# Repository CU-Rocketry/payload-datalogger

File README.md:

# payload-datalogger

Wirelessly configurable thermocouple data logging PCB implementing four MCP96RL00T on-board thermocouple to I2C converter ICs, an ESP32-C3 MCU, and flash storage.

## Screenshots

## BOM

See [this spreadsheet].(https://docs.google.com/spreadsheets/d/12Mr7GmqM8tnob1ocJkmMWgOL1p1aouqN9iYZXRkocOg/edit?usp=sharing)

**BOM cost:** $65 (on DigiKey, for two boards with attrition)
Does not include cables.

Additionally, batteries should be purchased elsewhere such as the suggested Amazon links to remain economical.

## Firmware

Firmware source code is located in the `src/payload-datalogger` directory.
Source code, for ease of modification by all team members, relies on the Arduino hardware abstraction layer (HAL).
The PlatformIO IDE and toolchain is required to build and debug the firmware, meaning that the minimum prerequisites for payload datalogger firmware development are:
- [Visual Studio Code](https://code.visualstudio.com/download)
- [PlatformIO IDE extension](https://marketplace.visualstudio.com/items?itemName=platformio.platformio-ide)

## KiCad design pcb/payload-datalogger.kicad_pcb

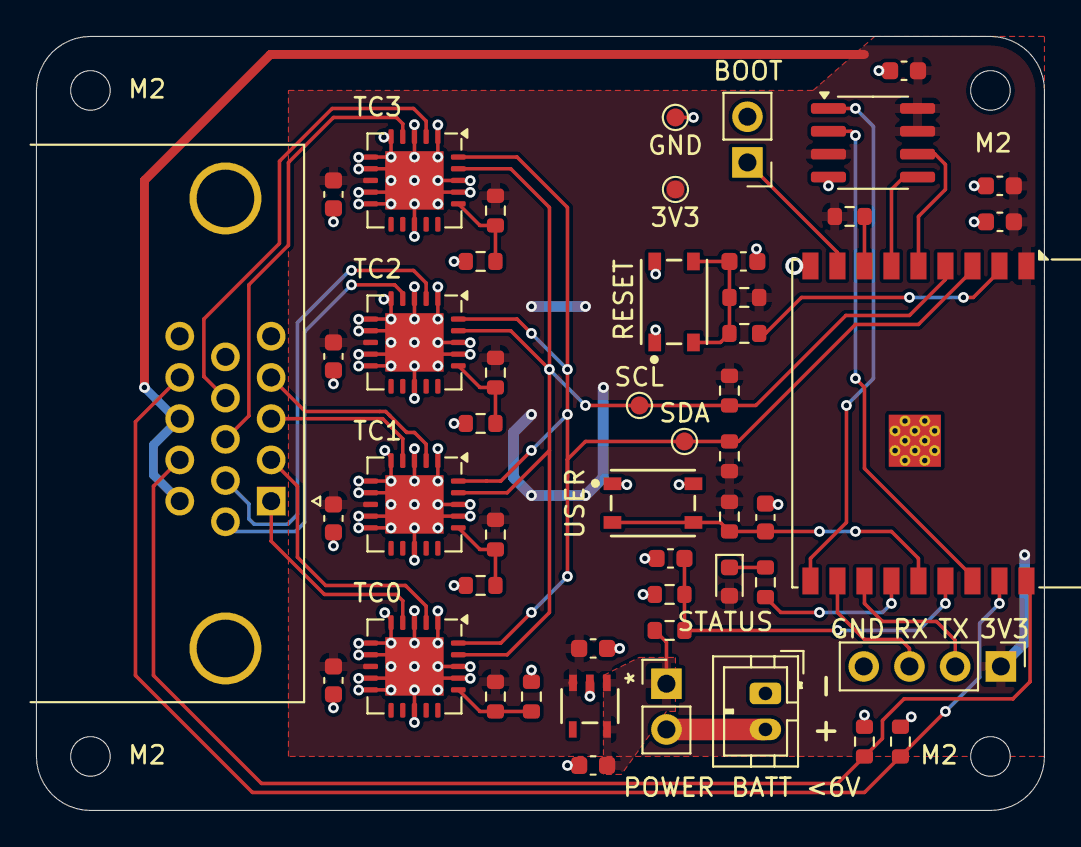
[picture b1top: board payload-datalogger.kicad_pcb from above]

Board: 2 copper layers, 56.0 x 43.0 mm, 50 parts (0 on the bottom side), 34 nets.

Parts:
BT1: 3.7V; JST_PH_B2B-PH-K_1x02_P2.00mm_Vertical
C1, C9, C12, C14: 100n; C_0603_1608Metric
C2, C3, C4, C5, C6, C7, C8: 1u; C_0603_1608Metric
C13: 10u; C_0603_1608Metric
D2: B1911USD; LED_0603_1608Metric
J1: 2.54mm 01x02 header; PinHeader_1x02_P2.54mm_Vertical
J2: DE15 Socket; DSUB-15-HD_Socket_Horizontal_P2.29x2.54mm_EdgePinOffset8.35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
J3: Conn_01x04_Pin; PinHeader_1x04_P2.54mm_Vertical
J4: Conn_01x02_Pin; PinHeader_1x02_P2.54mm_Vertical
R1, R2: 4.7k; R_0603_1608Metric
R3, R4, R7, R9, R11, R13, R14, R15, R16, R18, R19: 10k; R_0603_1608Metric
R5: DNP; R_0603_1608Metric
R6: 0; R_0603_1608Metric
R8: 2.2k; R_0603_1608Metric
R10: 4.3k; R_0603_1608Metric
R12: 7.5k; R_0603_1608Metric
R20: 270; R_0603_1608Metric
SW2, SW3: PTS815; SW_Push_PTS815_SJM_250_SMTR_LFS
TP1: 3V3; TestPoint_Pad_D1.0mm
TP2: GND; TestPoint_Pad_D1.0mm
TP3: I2C_SCL; TestPoint_Pad_D1.0mm
TP4: I2C_SDA; TestPoint_Pad_D1.0mm
U2: BU33SD5; SSOP5_ROM
U3: W25X40CLSN; SOIC-8_3.9x4.9mm_P1.27mm
U4, U5, U6, U7: MCP96RL00T-E_MX; TQFN-20-1EP_5x5mm_P0.65mm_EP3.25x3.25mm
U8: ESP32-C3-WROOM-02

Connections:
+3V3: C3.1, C4.1, C5.1, C6.1, C7.1, C8.1, C13.1, C14.1, D2.2 (A), J2.11, J2.13, J3.1, R1.1, R2.1, R5.2, R7.2, R9.2, R11.2, R15.1, R16.2, R19.1, TP1.1, U2.3 (VOUT), U3.3 (~WP), U3.7 (~HOLD), U3.8 (VCC), U4.8 (VDD), U5.8 (VDD), U6.8 (VDD), U7.8 (VDD), U8.1 (3V3)
+BATT: C2.1, J1.1, R3.1, U2.1 (VIN), U2.5 (STDBY)
/BATT_MEAS: C1.1, R3.2, R4.1, U8.15 (IO3)
/BOOT: J4.1, U8.8 (IO9)
/EN: R18.2, U8.2 (EN)
/FLASH_CLK: U3.6 (CLK), U8.5 (IO6)
/FLASH_CS: U3.1 (~CS), U8.10 (IO10)
/FLASH_DI: U3.5 (DI/IO_{0}), U8.6 (IO7)
/FLASH_DO: U3.2 (DO/IO_{1}), U8.16 (IO2)
/I2C_SCL: R1.2, TP3.1, U4.19 (SCL), U5.19 (SCL), U6.19 (SCL), U7.19 (SCL), U8.4 (IO5)
/I2C_SDA: R2.2, TP4.1, U4.20 (SDA), U5.20 (SDA), U6.20 (SDA), U7.20 (SDA), U8.3 (IO4)
/NTC0-: J2.12, R13.1, U8.18 (IO0)
/NTC1-: J2.14, R14.1, U8.17 (IO1)
/RXD: J3.3, U8.11 (IO20/RXD)
/TC0+: J2.2, U4.2 (VIN+)
/TC0-: J2.1, U4.4 (VIN-)
/TC1+: J2.4, U5.2 (VIN+)
/TC1-: J2.3, U5.4 (VIN-)
/TC2+: J2.7, U6.2 (VIN+)
/TC2-: J2.6, U6.4 (VIN-)
/TC3+: J2.9, U7.2 (VIN+)
/TC3-: J2.8, U7.4 (VIN-)
/TXD: J3.2, U8.12 (IO21/TXD)
/Thermocouple0/I2C_ADDR: R5.1, R6.2, U4.16 (ADDR)
/Thermocouple1/I2C_ADDR: R7.1, R8.2, U5.16 (ADDR)
/Thermocouple2/I2C_ADDR: R9.1, R10.2, U6.16 (ADDR)
/Thermocouple3/I2C_ADDR: R11.1, R12.2, U7.16 (ADDR)
/USER_BTN: C9.1, R15.2, SW2.2, U8.14 (IO19)
/USER_LED: R20.2, U8.13 (IO18)
GND: BT1.1 (+), C1.2, C2.2, C3.2, C4.2, C5.2, C6.2, C7.2, C8.2, C9.2, C12.2, C13.2, C14.2, J2.0, J3.4, J4.2, R4.2, R6.1, R8.1, R10.1, R12.1, R13.2, R14.2, SW2.1, SW3.1, TP2.1, U2.2 (GND), U3.4 (GND), U4.1 (GND), U4.3 (GND), U4.5 (GND), U4.6 (GND), U4.7 (GND), U4.9 (GND), U4.10 (GND), U4.13 (GND), U4.17 (GND), U4.18 (GND), U4.21 (EP), U5.1 (GND), U5.3 (GND), U5.5 (GND), U5.6 (GND), U5.7 (GND), U5.9 (GND), U5.10 (GND), U5.13 (GND), U5.17 (GND), U5.18 (GND), U5.21 (EP), U6.1 (GND), U6.3 (GND), U6.5 (GND), U6.6 (GND), U6.7 (GND), U6.9 (GND), U6.10 (GND), U6.13 (GND), U6.17 (GND), U6.18 (GND), U6.21 (EP), U7.1 (GND), U7.3 (GND), U7.5 (GND), U7.6 (GND), U7.7 (GND), U7.9 (GND), U7.10 (GND), U7.13 (GND), U7.17 (GND), U7.18 (GND), U7.21 (EP), U8.9 (GND), U8.19 (GND)
unnamed: BT1.2 (-), J1.2
unnamed: C12.1, R16.1, R18.1, SW3.2
unnamed: D2.1 (K), R20.1
unnamed: R19.2, U8.7 (IO8)

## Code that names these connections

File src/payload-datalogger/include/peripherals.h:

#ifndef PERIPHERALS_H
#define PERIPHERALS_H

// ADC
#define NTC_0_PIN 0
#define NTC_1_PIN 1
#define BATT_MEAS_PIN 3

// SPI
#define FLASH_DO 2
#define FLASH_CLK 6
#define FLASH_DI 7
#define FLASH_CS 10

// I2C
#define I2C_SCL 5
#define I2C_SDA 4

// GPIO
#define USER_LED_PIN 18
#define USER_BUTTON_PIN 19

#endif

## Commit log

2025-04-01 Add PCB
2025-04-01 Update kicad-library-sigmondkukla
2025-04-01 Add readme and screenshots
2025-04-01 Connect flash decoupling cap to GND
2025-04-01 Reroute battery measure
2025-04-01 Tweak battery
2025-04-01 Add rounded corners and 3.3V stitching
2025-04-01 Update schematic for DE15
2025-04-01 Update PCB to use d sub
2025-04-02 Remove locks
2025-04-02 Add user button debounce to sch
2025-04-02 Add PCB button debounce
2025-04-03 Move D-sub further out
2025-04-03 Create production files
2025-04-03 Increase thermal vias to 0.3mm hole
2025-04-03 Generate new production files
2025-04-03 Use larger Dsub for BOM optimization
2025-04-04 Prevent mounting hole overlap with dsub
2025-04-04 Add ESP32-C3 3D model
2025-04-07 Switch to ESP32 C3 WROOM module
2025-04-07 Increase ESP32 thermal pad via hole size
2025-04-07 New bom
2025-04-07 Rearrange battery and LDO
2025-04-07 Update screenshots
2025-04-07 Fix silkscreen overlap in DRC
2025-04-07 Add BOM to readme
2025-04-07 Update production files
2025-04-07 Add USB to UART bridge to BOM on github
2025-04-07 Fix TC2 routing and D-sub numbering
2025-04-07 Ignore lock files
2025-04-07 Link spreadsheet in readme
2025-04-07 Fixed planes etc
2025-04-07 Ordered PCB
2025-04-14 Add datasheets
2025-04-17 Implement web and peripheral framework
2025-04-17 Add SPIFlash
2025-04-25 add flash datasheet
2025-04-25 Refactor
2025-05-14 Add data export feature
2025-05-14 Improve documentation
2025-05-14 Move LED and button init out of constructor
2025-05-14 Add status LED blinking
2025-06-08 Storage tweaks
2025-07-16 Testing at comp
2025-07-16 Update kicad library
